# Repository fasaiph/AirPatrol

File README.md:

# AirPatrol
An add-on to a drone so you can measure air quality remotely!

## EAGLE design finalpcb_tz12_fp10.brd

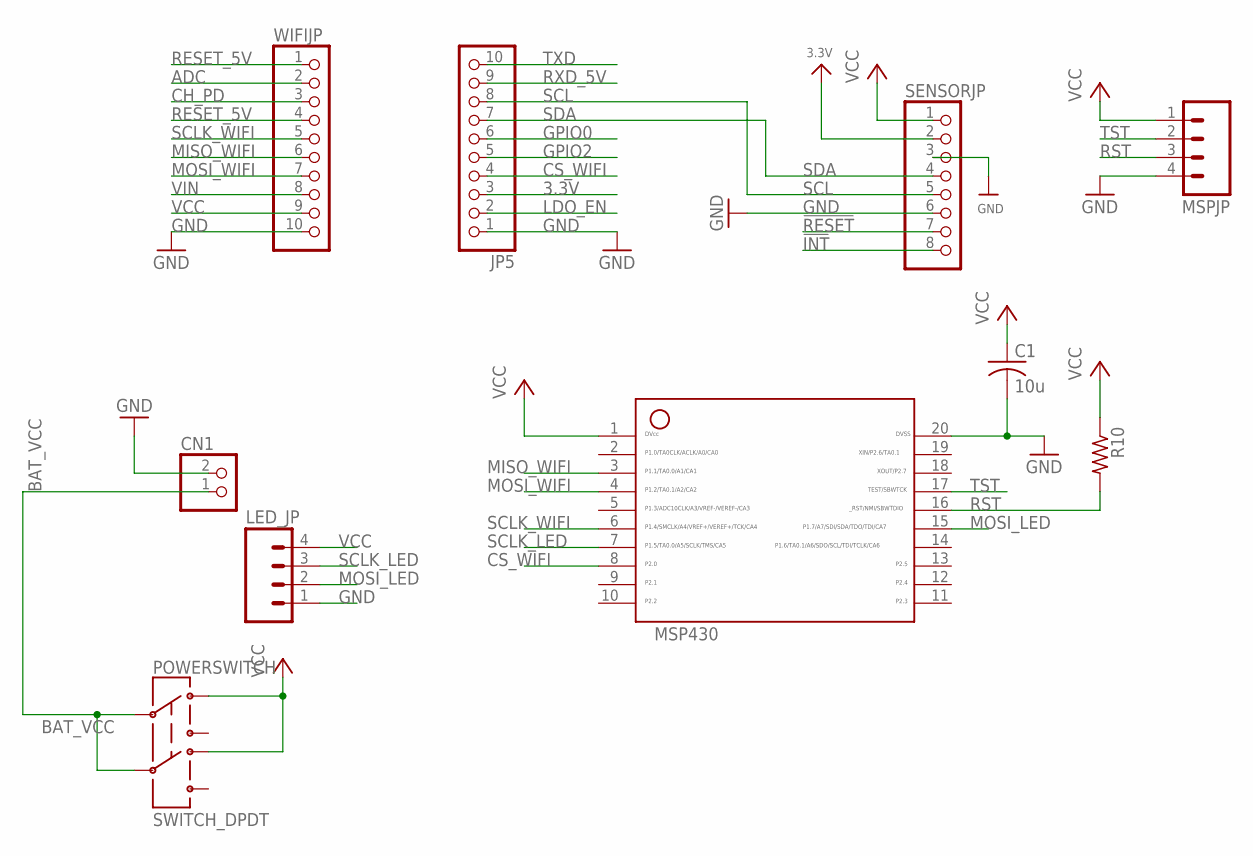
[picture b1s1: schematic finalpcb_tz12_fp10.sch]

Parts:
C1: 10u; C1206
CN1: JST_2PIN-SMT-RA; JST-PH-2-SMT-RA
JP5: HEADER-1X1070MIL; 1X10_ROUND70
LED_JP: PENDANT_M04LOCK; PENDANT_1X04_LOCK
MSP430: RATDBS_MSP430; RATDBS_20_PIN
MSPJP: PENDANT_M04LOCK; PENDANT_1X04_LOCK
POWERSWITCH: SWITCH_DPDT; JS_DPDT_TH
R10: R-US_R1206; R1206
SENSORJP: HEADER-1X870MIL; 1X08_ROUND_70
WIFIJP: HEADER-1X1070MIL; 1X10_ROUND70

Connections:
3.3V: JP5.3, SENSORJP.2
!INT: SENSORJP.8
!RESET: SENSORJP.7
ADC: WIFIJP.2
BAT_VCC: CN1.1 (2), POWERSWITCH.2, POWERSWITCH.5
CH_PD: WIFIJP.3
CS_WIFI: JP5.4, MSP430.8
GND: C1.2, CN1.2 (1), JP5.1, LED_JP.1, MSP430.20, MSPJP.4, SENSORJP.3, SENSORJP.6, WIFIJP.10
GPIO0: JP5.6
GPIO2: JP5.5
LDO_EN: JP5.2
MISO_WIFI: MSP430.3, WIFIJP.6
MOSI_LED: LED_JP.2, MSP430.15
MOSI_WIFI: MSP430.4, WIFIJP.7
RESET_5V: WIFIJP.1, WIFIJP.4
RST: MSP430.16, MSPJP.3, R10.2
RXD_5V: JP5.9
SCL: JP5.8, SENSORJP.5
SCLK_LED: LED_JP.3, MSP430.7
SCLK_WIFI: MSP430.6, WIFIJP.5
SDA: JP5.7, SENSORJP.4
TST: MSP430.17, MSPJP.2
TXD: JP5.10
VCC: C1.1, LED_JP.4, MSP430.1, MSPJP.1, POWERSWITCH.1, POWERSWITCH.4, R10.1, SENSORJP.1, WIFIJP.9
VIN: WIFIJP.8

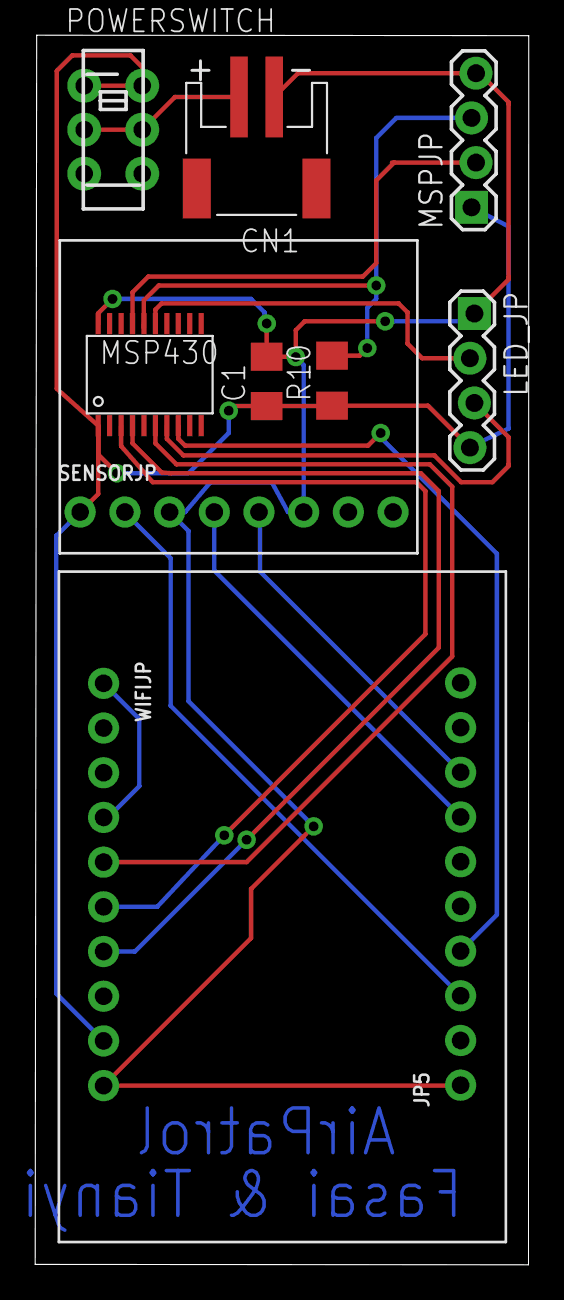
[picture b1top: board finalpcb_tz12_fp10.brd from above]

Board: 2 copper layers, 28.0 x 69.9 mm, 10 parts (0 on the bottom side), 15 nets.

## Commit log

2018-09-13 Rename finalpcb_tz12_fp10.GBL to PCB/finalpcb_tz12_fp10.GBL
2018-09-13 Rename finalpcb_tz12_fp10.GML to PCB/finalpcb_tz12_fp10.GML
2018-09-13 Rename finalpcb_tz12_fp10.GTL to PCB/finalpcb_tz12_fp10.GTL
2018-09-13 Rename finalpcb_tz12_fp10.TXT to PCB/finalpcb_tz12_fp10.TXT
2018-09-13 Rename finalpcb_tz12_fp10.brd to PCB/finalpcb_tz12_fp10.brd
2018-09-13 Rename finalpcb_tz12_fp10.dri to PCB/finalpcb_tz12_fp10.dri
2018-09-13 Rename finalpcb_tz12_fp10.gpi to PCB/finalpcb_tz12_fp10.gpi
2018-09-13 Rename finalpcb_tz12_fp10.sch to PCB/finalpcb_tz12_fp10.sch

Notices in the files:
parts and their libraries:
microbuilder: This work is placed in the public domain, and may be freely used for commercial and non-commercial work with the following conditions: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
